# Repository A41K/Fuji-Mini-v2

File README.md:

THIS WAS BUILT FOR ARDUINO / ESP-32 SOFTWARE
ANY ISSUES FOUND PLEASE REPORT IT TO ME

## Fuji Mini v2

A small Pocket-sized Music player in the palm of your hands

Main Features:
- ESP-32-S1-WROOM as MCU
- Boot / Reset onboard buttons
- Built in DAP, Battery managment, Charger, AMP
- 0.91 inch Screen
- Re-programable software (/Firmware/firmware.ino)
- micro-SD card reading functionality
- USB-C for charging
- Battery indicator LED
- Rotary + Button for controls and volume
- Play / Forward buttons seperately
- 3.5 inch Headphone jack for analog sound

## Schematic:

- The schematic is organized and labeled with the different parts and uses
- You can use the other unused GPIO pins (didn't put a no flag for that)

## PCB:

- Everything can be hand soldered and put on.
- Only the battery connector is on the other side

- You need the exact amount of caps and res with the specific values to build it. Check the BOM.csv for that

## BOM:

| Part | What it's for | Qty | Unit | Total | Vendor |
| --- | --- | --- | --- | --- | --- |
| [Battery connector](https://hqelektronika.hu/csatlakozok/egyeb-csatlakozok/csat-17021b90-egysoros-csatlakozo-aljzat-apa-pcb-jst-ph-2p-tav-2-0mm-90?cid=18094&cikkszam=CSAT-17021%2FB90) | Connector | 2 | $0.21 | $0.42 | HQelektronika |
| [10uF](https://hqelektronika.hu/passziv-alkatreszek/kondenzatorok/smd-keramia-kondenzatorok/smdc-10uf-0805-25-smd-kondenzator-25v-10uf-10-x5r?cid=75979&cikkszam=SMDC+10UF+0805-25) | Capacitor | 5 | $0.06 | $0.30 | HQelektronika |
| [100nF](https://hqelektronika.hu/passziv-alkatreszek/kondenzatorok/smd-keramia-kondenzatorok/smdc-100n-0805-smd-kondenzator-50v-100nf-10-x7r?cid=47620&cikkszam=SMDC+100N+0805) | Capacitor | 8 | $0.03 | $0.24 | HQelektronika |
| [1uF](https://hqelektronika.hu/passziv-alkatreszek/kondenzatorok/smd-keramia-kondenzatorok/smdc-1-0u-0805-25-smd-kondenzator-25v-1uf-10-x7r?cid=75996&cikkszam=SMDC+1.0U+0805-25) | Capacitor | 5 | $0.04 | $0.20 | HQelektronika |
| [2.2uF](https://hqelektronika.hu/passziv-alkatreszek/kondenzatorok/smd-keramia-kondenzatorok/smdc-2-2u-0805-smd-kondenzator-25v-2-2uf-10-x7r?cid=47660&cikkszam=SMDC+2.2U+0805) | Capacitor | 5 | $0.05 | $0.25 | HQelektronika |
| [220uF](https://hqelektronika.hu/passziv-alkatreszek/kondenzatorok/elektrolit-kondenzator/22016smd-105-elektrolit-kondenzator-220uf-16v-105c-smd6-3?cid=1853&cikkszam=220%2F16SMD-105) | Capacitor | 2 | $0.22 | $0.44 | HQelektronika |
| [Micro_SD_Card](https://www.hestore.hu/prod_10035282.html) | MicroSD card connector | 1 | $2.00 | $2.00 | hestore |
| [AudioJack](https://hqelektronika.hu/csatlakozok/audio-video-csatlakozok/jc-1132s-jack-3-5mm-aljzat-sztereo-nyakos-smd?cid=28732&cikkszam=JC-113%2F2S) | 3.5 mm jack | 1 | $1.71 | $1.71 | HQelektronika |
| [10k](https://hqelektronika.hu/passziv-alkatreszek/ellenallasok/smd-ellenallasok/smd-10k-0805-1-0-125w-thick-film-0805-smd-ellenallas-10k-1) | Resistor | 15 | $0.02 | $0.30 | HQelektronika |
| [20k](https://hqelektronika.hu/passziv-alkatreszek/ellenallasok/smd-ellenallasok/smd-22k-0805-0-125w-chip-ellenallas-22k-5?cid=47440&cikkszam=SMD+22K+0805) | Resistor | 10 | $0.01 | $0.10 | HQelektronika |
| [4.7k](https://hqelektronika.hu/passziv-alkatreszek/ellenallasok/smd-ellenallasok/smd-4k7-0805-0-125w-thick-film-0805-smd-ellenallas-4-7k-5?cid=47526&cikkszam=SMD+4K7+0805) | Resistor | 10 | $0.01 | $0.10 | HQelektronika |
| [2k](https://hqelektronika.hu/passziv-alkatreszek/ellenallasok/smd-ellenallasok/smd-2k2-0805-0-125w-thick-film-0805-smd-ellenallas-2-2k-5?cid=47461&cikkszam=SMD+2K2+0805) | Resistor | 10 | $0.02 | $0.20 | HQelektronika |
| [1k](https://hqelektronika.hu/passziv-alkatreszek/ellenallasok/smd-ellenallasok/smd-1k-0805-0-125w-thick-film-0805-smd-ellenallas-1k-5?cid=47416&cikkszam=SMD+1K+0805) | Resistor | 10 | $0.02 | $0.20 | HQelektronika |
| [5.1k](https://hqelektronika.hu/passziv-alkatreszek/ellenallasok/smd-ellenallasok/smd-5k1-0805-0-125w-thick-film-0805-smd-ellenallas-5-1k-5?cid=78466&cikkszam=SMD+5K1+0805) | Resistor | 10 | $0.02 | $0.20 | HQelektronika |
| [ESP32-S3-WROOM-1](https://shop.ret.hu/aktiv-alkatreszek-integralt-aramkorok-modulok/analog-integralt-aramkorok/hang--es-nagyfrekvencias_rf_-aramkorok-modulok/rf-modulok/76-16-65) | Microcontroller | 1 | $6.02 | $6.02 | shop.ret.hu |
| [PCM5102A](https://www.microcontroller.hu/termek/pcm5102a-i2s-dac-internet-radio-modul/) | DAC decoder | 1 | $4.57 | $4.57 | microcontroller.hu |
| [TPA6110A2DGN](https://www.aliexpress.com/item/1005010338743602.html) | Amplifier | 1 | $1.50 | $1.50 | AliExpress |
| [ER_OLEDM0.91_1x-I2C](https://sigmanortec.ro/hu/kijelzo-oled-iic-i2c-091-128x32?SubmitCurrency=1&id_currency=4) | Display | 1 | $4.23 | $4.23 | sigmanortec |
| [MCP73831-2-MC](https://hu.rs-online.com/web/p/akkumulatorkezeles/7386360) | Charging module | 1 | $3.93 | $3.93 | RS Online |
| [AP2112K-3.3](https://www.hestore.hu/prod_10047483.html) | Voltage regulator | 1 | $0.41 | $0.41 | hestore |
| [U262-161N-4BVC11](https://jlcpcb.com/partdetail/U262-161N-4BVC11/C319148) | USB-C connector | 1 | $0.39 | $0.39 | JLCPCB |
| **Parts subtotal** | | | | **$27.71** | |
| **Tax & shipping** | | | | **$5.28** | |
| **Total** | | | | **$32.99** | |

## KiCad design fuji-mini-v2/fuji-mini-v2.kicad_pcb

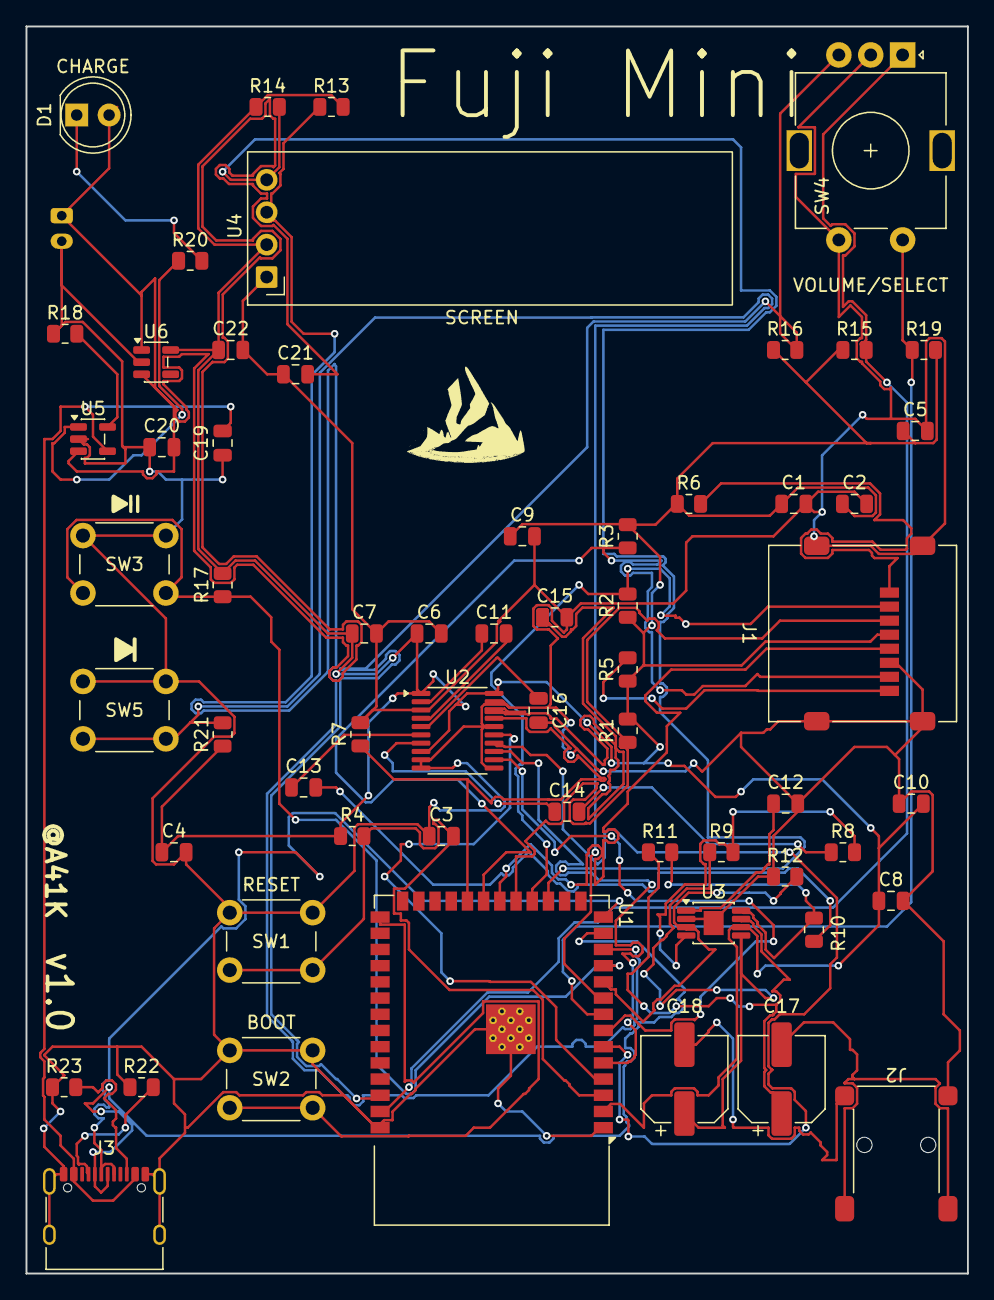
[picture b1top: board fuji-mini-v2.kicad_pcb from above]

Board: 2 copper layers, 73.8 x 97.7 mm, 61 parts (1 on the bottom side), 47 nets.

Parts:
BT1: Battery_Cell; JST_PH_S2B-PH-K_1x02_P2.00mm_Horizontal
C1, C5, C20, C22: 10uF; C_0805_2012Metric
C2, C4, C6, C7, C8, C9, C10, C15: 100nF; C_0805_2012Metric
C3, C12, C13, C14, C21: 1uF; C_0805_2012Metric
C11, C16: 2.2uF; C_0805_2012Metric
C17, C18: 220uF; CP_Elec_6.3x7.7
C19: 4.7uF; C_0805_2012Metric
D1: LED; LED_D5.0mm
J1: Micro_SD_Card; microSD_HC_Molex_47219-2001
J2: AudioJack3_SwitchT; Jack_3.5mm_Lumberg_1503_02_Horizontal
J3: USB_C_Receptacle_USB2.0_14P; USB_C_Receptacle_XKB_U262-16XN-4BVC11
R1, R2, R3, R4, R5, R6, R7, R9, R11, R12, R15, R16, R17, R19, R21: 10k; R_0805_2012Metric
R8, R10: 20k; R_0805_2012Metric
R13, R14: 4.7k; R_0805_2012Metric
R18: 2k; R_0805_2012Metric
R20: 1k; R_0805_2012Metric
R22, R23: 5.1k; R_0805_2012Metric
SW1, SW2, SW3, SW5: SW_Push; SW_PUSH_6mm
SW4: RotaryEncoder_Switch; RotaryEncoder_Alps_EC11E-Switch_Vertical_H20mm
U1: ESP32-S3-WROOM-1
U2: PCM5102A; TSSOP-20_4.4x6.5mm_P0.65mm
U3: TPA6110A2DGN; HVSSOP-8-1EP_3x3mm_P0.65mm_EP1.57x1.89mm
U4: ER_OLEDM0.91_1x-I2C
U5: MCP73831-2-OT; SOT-23-5
U6: AP2112K-3.3; SOT-23-5

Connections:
+3V3: C1.1, C2.1, C4.1, C5.1, C6.1, C7.1, C8.1, C9.1, C10.2, C22.1, J1.4 (VDD), R1.2, R2.1, R3.2, R4.1, R5.1, R6.1, R13.2, R14.1, R15.1, R16.1, R17.2, R19.2, R21.1, U1.2 (3V3), U2.1 (CPVDD), U2.8 (AVDD), U2.20 (DVDD), U3.6 (VDD), U4.2 (VCC), U6.5 (VOUT)
AMP_ENABLE: R12.2, U1.10 (IO17), U3.3 (SHDN)
BTN_NEXT: R21.2, SW5.2, U1.9 (IO16)
BTN_PLAY: R17.1, SW3.2, U1.11 (IO18)
DAC_MUTE: R7.1, U1.22 (IO14), U2.17 (XSMT)
DAC_OUTL: C13.2, R10.1
DAC_OUTR: C14.2, R8.1
ENC_A: R15.2, SW4.A, U1.39 (IO1)
ENC_B: R16.2, SW4.B, U1.38 (IO2)
ENC_BTN: R19.1, SW4.S2, U1.8 (IO15)
GND: BT1.2 (-), C1.2, C2.2, C3.1, C4.2, C5.2, C6.2, C7.2, C8.2, C9.2, C10.1, C12.2, C15.2, C16.2, C19.1, C20.1, C21.1, C22.2, J1.6 (VSS), J1.SH (SHIELD), J2.S, J3.A1 (GND), J3.A12 (GND), J3.B1 (GND), J3.B12 (GND), J3.SH (SHIELD), R7.2, R12.1, R18.1, R22.1, R23.1, SW1.1, SW2.1, SW3.1, SW4.C, SW4.S1, SW5.1, U1.1 (GND), U1.40 (GND), U1.41 (GND), U2.3 (CPGND), U2.9 (AGND), U2.10 (DEMP), U2.11 (FLT), U2.16 (FMT), U2.19 (DGND), U3.2 (GND), U3.9 (GND), U4.1 (GND), U5.2 (V_{SS}), U6.2 (GND)
GPIO10: J1.2 (DAT3/CD), R2.2, U1.18 (IO10)
GPIO11: J1.3 (CMD), R1.1, U1.19 (IO11)
GPIO12: J1.5 (CLK), U1.20 (IO12)
GPIO13: J1.7 (DAT0), R3.1, U1.21 (IO13)
HP_L: C17.2, J2.T
HP_R: C18.2, J2.R
I2C_SCL: R13.1, U1.12 (IO8), U4.3 (SCL)
I2C_SDA: R14.2, U1.17 (IO9), U4.4 (SDA)
I2S_BCK: U1.5 (IO5), U2.13 (BCK)
I2S_DIN: U1.6 (IO6), U2.14 (DIN)
I2S_LRCK: U1.4 (IO4), U2.15 (LRCK)
I2S_SCK: U1.7 (IO7), U2.12 (SCK)
unnamed: D1.1 (K), R20.2
unnamed: J1.8 (DAT1), R5.2
unnamed: J1.1 (DAT2), R6.2
unnamed: J3.A5 (CC1), R22.2
unnamed: J3.B5 (CC2), R23.2
unnamed: C3.2, R4.2, SW1.2, U1.3 (EN)
unnamed: SW2.2, U1.27 (IO0)
unnamed: C11.2, U2.4 (CAPM)
unnamed: C11.1, U2.2 (CAPP)
unnamed: C15.1, U2.18 (LDOO)
unnamed: C13.1, U2.6 (OUTL)
unnamed: C14.1, U2.7 (OUTR)
unnamed: C16.1, U2.5 (VNEG)
unnamed: C12.1, U3.1 (BYPASS)
unnamed: R10.2, R11.2, U3.8 (IN1-)
unnamed: R8.2, R9.2, U3.4 (IN2-)
unnamed: R18.2, U5.5 (PROG)
unnamed: R20.1, U5.1 (STAT)
USB_DN: J3.A7 (D-), J3.B7 (D-), U1.13 (USB_D-)
USB_DP: J3.A6 (D+), J3.B6 (D+), U1.14 (USB_D+)
VBAT: BT1.1 (+), C20.2, C21.2, D1.2 (A), U5.3 (V_{BAT}), U6.1 (VIN), U6.3 (EN)
VDD: C19.2, J3.A4 (VBUS), J3.A9 (VBUS), J3.B4 (VBUS), J3.B9 (VBUS), U5.4 (V_{DD})
VO1: C17.1, R11.1, U3.7 (VO1)
VO2: C18.1, R9.1, U3.5 (VO2)

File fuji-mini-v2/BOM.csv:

"Reference","Qty","Value","DNP","Exclude from BOM","Exclude from Board","Footprint","Datasheet"
"BT1","1","Battery_Cell","","","","Connector_JST:JST_PH_S2B-PH-K_1x02_P2.00mm_Horizontal",""
"C1,C5,C20","3","10uF","","","","Capacitor_SMD:C_0805_2012Metric",""
"C2,C4,C6,C7,C8,C9,C10,C15","8","100nF","","","","Capacitor_SMD:C_0805_2012Metric",""
"C3,C12,C13,C14,C21,C22","6","1uF","","","","Capacitor_SMD:C_0805_2012Metric",""
"C11,C16","2","2.2uF","","","","Capacitor_SMD:C_0805_2012Metric",""
"C17,C18","2","220uF","","","","Capacitor_THT:CP_Radial_D6.3mm_P2.50mm",""
"C19","1","4.7uF","","","","Capacitor_SMD:C_0805_2012Metric",""
"D1","1","LED","","","","LED_THT:LED_D5.0mm",""
"J1","1","Micro_SD_Card","","","","Connector_Card:microSD_HC_Hirose_DM3AT-SF-PEJM5","https://www.we-online.com/components/products/datasheet/6930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"
"J2","1","AudioJack3_SwitchT","","","","Connector_Audio:Jack_3.5mm_CUI_SJ1-3535NG_Horizontal",""
"J3","1","USB_C_Receptacle_USB2.0_14P","","","","Connector_USB:USB_C_Receptacle_XKB_U262-16XN-4BVC11","https://www.usb.org/sites/default/files/documents/usb_type-c.zip"
"R1,R2,R3,R4,R5,R6,R7,R9,R11,R12,R15,R16,R17,R19,R21","15","10k","","","","Resistor_SMD:R_0805_2012Metric",""
"R8,R10","2","20k","","","","Resistor_SMD:R_0805_2012Metric",""
"R13,R14","2","4.7k","","","","Resistor_SMD:R_0805_2012Metric",""
"R18","1","2k","","","","Resistor_SMD:R_0805_2012Metric",""
"R20","1","1k","","","","Resistor_SMD:R_0805_2012Metric",""
"R22,R23","2","5.1k","","","","Resistor_SMD:R_0805_2012Metric",""
"SW1,SW2,SW3,SW5","4","SW_Push","","","","Button_Switch_THT:SW_PUSH_6mm",""
"SW4","1","RotaryEncoder_Switch","","","","Rotary_Encoder:RotaryEncoder_Alps_EC11E-Switch_Vertical_H20mm",""
"U1","1","ESP32-S3-WROOM-1","","","","RF_Module:ESP32-S3-WROOM-1","https://www.espressif.com/sites/default/files/documentation/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"
"U2","1","PCM5102A","","","","Package_SO:TSSOP-20_4.4x6.5mm_P0.65mm","https://www.ti.com/lit/ds/symlink/pcm5102a.pdf"
"U3","1","TPA6110A2DGN","","","","Package_SO:HVSSOP-8-1EP_3x3mm_P0.65mm_EP1.57x1.89mm","https://www.ti.com/lit/ds/symlink/tpa6110a2.pdf"
"U4","1","ER_OLEDM0.91_1x-I2C","","","","Display:ER_OLEDM0.91_1x-I2C","https://www.buydisplay.com/download/manual/ER-OLEDM0.91-1_Da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"
"U5","1","MCP73831-2-MC","","","","Package_DFN_QFN:DFN-8-1EP_3x2mm_P0.5mm_EP1.7x1.4mm","http://ww1.microchip.com/downloads/en/DeviceDoc/20001984g.pdf"
"U6","1","AP2112K-3.3","","","","Package_TO_SOT_SMD:SOT-23-5","https://www.diodes.com/assets/Datasheets/AP2112.pdf"

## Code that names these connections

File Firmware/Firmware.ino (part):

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#define BAT_SHUTDOWN_MV     3500

// Pins (minus those who I didn't connect (you can use them minus the io3))
#define PIN_I2S_LRCK    4
#define PIN_I2S_BCK     5
#define PIN_I2S_DIN     6
#define PIN_I2S_SCK     7

#define PIN_I2C_SCL     8
#define PIN_I2C_SDA     9

#define PIN_SD_CS       10
#define PIN_SD_MOSI     11
#define PIN_SD_CLK      12
#define PIN_SD_MISO     13

#define PIN_DAC_MUTE    14
#define PIN_ENC_BTN     15
#define PIN_BTN_NEXT    16
#define PIN_AMP_EN      17
#define PIN_BTN_PLAY    18

#define PIN_ENC_A       1
#define PIN_ENC_B       2
#define PIN_BAT_SENSE   3

Audio audio;
SPIClass spiSD(FSPI);
U8G2_SSD1306_128X32_UNIVISION_F_HW_I2C oled(U8G2_R0, U8X8_PIN_NONE, PIN_I2C_SCL, PIN_I2C_SDA);
Preferences prefs;

std::vector<String> tracks;
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    bool takeLong() { bool e = longEvt; longEvt = false; return e; }
};

Button btnplay(PIN_BTN_PLAY);
Button btnNext(PIN_BTN_NEXT);
Button btnEnc(PIN_ENC_BTN);

// encoder
int8_t  encDelta = 0;
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const int8_t ENC_TABLE[16] = {0,-1,1,0,  1,0,0,-1,  -1,0,0,1,  0,1,-1,0};

void encoderUpdate() {
    encState = ((encState << 2) | (digitalRead(PIN_ENC_A) << 1) | digitalRead(PIN_ENC_B)) & 0x0F;
    static int8_t acc = 0;
    acc += ENC_TABLE[encState];
    if (acc >= 4)       { encDelta++; acc = 0; }
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// power for the audio (for the amp and dac)
void ampOn()    { digitalWrite(PIN_AMP_EN, HIGH); }
void ampOff()   { digitalWrite(PIN_AMP_EN, LOW); }
void dacMute()  { digitalWrite(PIN_DAC_MUTE, LOW); }
void dacUnmute() { digitalWrite(PIN_DAC_MUTE, HIGH); }

// helpers (for the audio files in /music)
// accepts .acc / .mp3 / .wav / .flac / .m4a
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    oled.setPowerSave(1);
    saveState();

    esp_sleep_enable_ext1_wakeup_io(1ULL << PIN_BTN_PLAY, ESP_EXT1_WAKEUP_ANY_LOW);
    esp_deep_sleep_start();
}

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
void setup() {
  pinMode(PIN_AMP_EN, OUTPUT);   ampOff();
  pinMode(PIN_DAC_MUTE, OUTPUT); dacMute();
  pinMode(PIN_I2S_SCK, OUTPUT);  digitalWrite(PIN_I2S_SCK, LOW);

  Serial.begin(115200);
  delay(200);
  Serial.println("\nFuji Mini starting");

  btnPlay.begin(); btnNext.begin(); btnEnc.begin();
  pinMode(PIN_ENC_A, INPUT);
  pinMode(PIN_ENC_B, INPUT);
#if HAS_BAT_SENSE
  analogReadResolution(12);
  analogSetPinAttenuation(PIN_BAT_SENSE, ADC_11db);
#endif

  Wire.begin(PIN_I2C_SDA, PIN_I2C_SCL, 400000);
  oled.begin();
  drawScreen("Fuji Mini", "Starting...");

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    if (tracks.empty()) drawScreen("No music found", "Put files in /music");
  }

  audio.setPinout(PIN_I2S_BCK, PIN_I2S_LRCK, PIN_I2S_DIN);
  audio.setVolume(volume);

  batteryUpdate();
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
